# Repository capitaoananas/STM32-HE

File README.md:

# STM 32 HE

A silly [hall effect](https://en.wikipedia.org/wiki/Hall_effect) split keyboard with a built in [STM32F446RET6](https://lcsc.com/product-detail/Microcontrollers-MCU-MPU-SOC_ST-STM32F446RET6_C69336.html?s_z=n_STM32F446RET6) that runs on the [libhmk](https://github.com/peppapighs/libhmk) firmware!

Schematic             |  PCB
:-------------------------:|:-------------------------:
  |  

If you really want to crunch in on those errors check the [kicanvas](https://kicanvas.org/?github=https%3A%2F%2Fgithub.com%2Fcapitaoananas%2FSTM32-HE%2Fblob%2Fmain%2Fkicad%2Fstm32-he.kicad_pro) file

---

## Hardware:

- STM32F446RET6
- OH49E-S
- SN74LV4051A
- TC2030
- TYPE-C-31-M-12
- USBLC6-2SC6
- X322516MLB4SI

---

This project is still a WIP

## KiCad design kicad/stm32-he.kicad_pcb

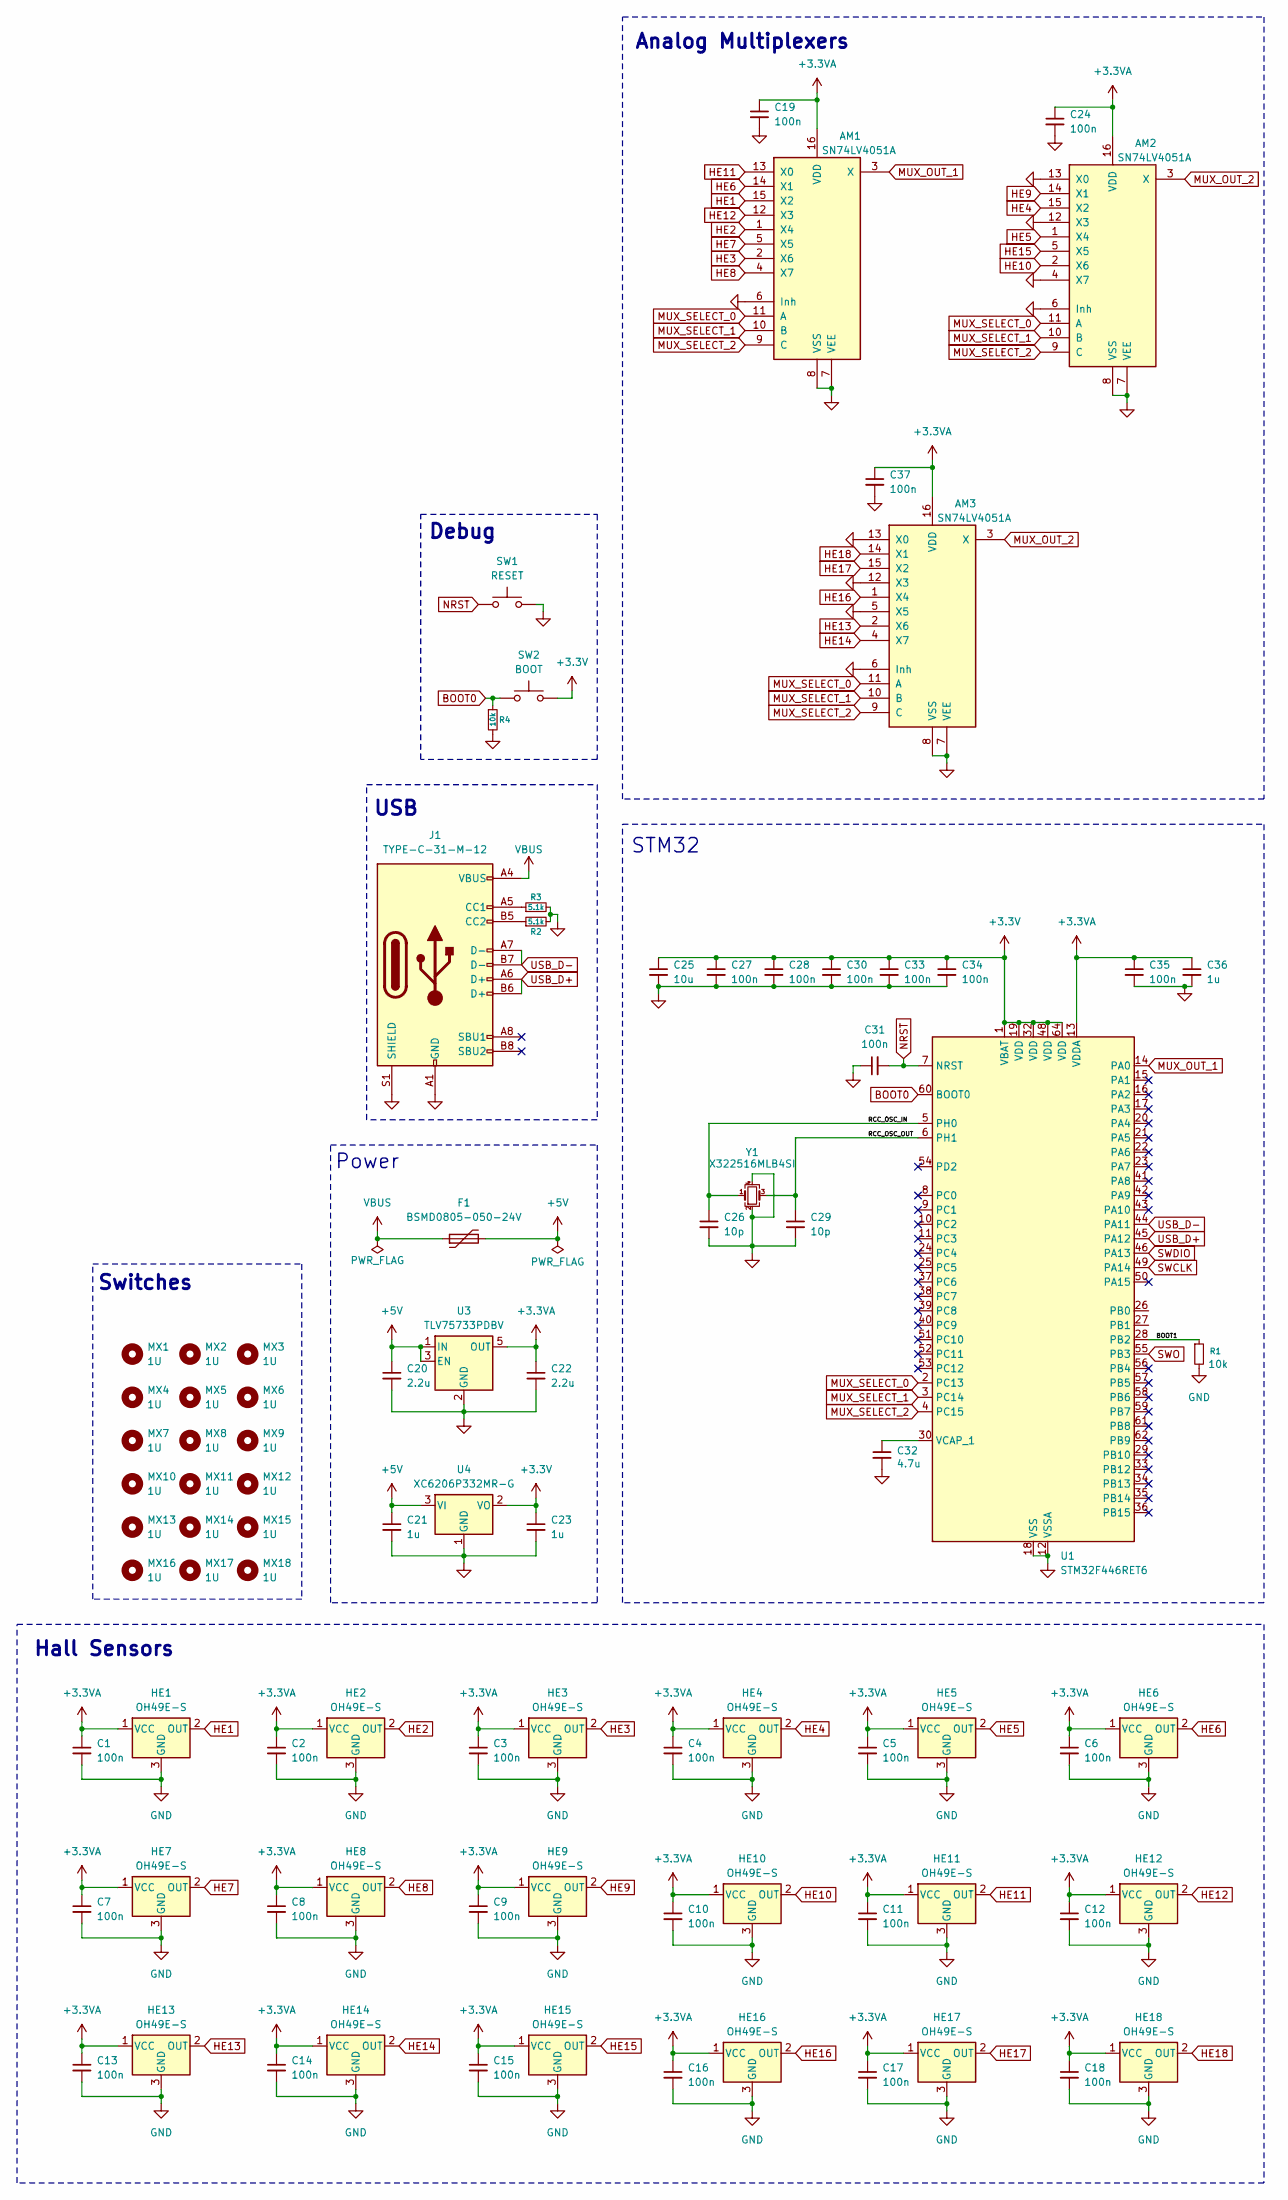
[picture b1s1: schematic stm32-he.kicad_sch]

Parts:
AM1, AM2, AM3: SN74LV4051A; TSSOP-16_4.4x5mm_P0.65mm
C1, C2, C3, C4, C5, C6, C7, C8, C9, C10, C11, C12, C13, C14, C15, C16, C17, C18, C19, C24, C27, C28, C30, C31, C33, C34, C35, C37: 100n; C_0402_1005Metric
C20, C22: 2.2u; C_0603_1608Metric
C21, C23, C36: 1u; C_0603_1608Metric
C25: 10u; C_0603_1608Metric
C26, C29: 10p; C_0402_1005Metric
C32: 4.7u; C_0603_1608Metric
F1: BSMD0805-050-24V; Fuse_0805_2012Metric
HE1, HE2, HE3, HE4, HE5, HE6, HE7, HE8, HE9, HE10, HE11, HE12, HE13, HE14, HE15, HE16, HE17, HE18: OH49E-S; SOT-23-3
J1: TYPE-C-31-M-12; USB_C_Receptacle_HRO_TYPE-C-31-M-12
MX1, MX2, MX3, MX4, MX5, MX6, MX7, MX8, MX9, MX10, MX11, MX12, MX13, MX14, MX15, MX16, MX17, MX18: 1U; MX-1U
R1, R4: 10k; R_0402_1005Metric
R2, R3: 5.1k; R_0402_1005Metric
SW1: RESET; SW_Push_1P1T_NO_CK_KMR2
SW2: BOOT; SW_Push_1P1T_NO_CK_KMR2
U1: STM32F446RET6; LQFP-64_10x10mm_P0.5mm
U3: TLV75733PDBV; SOT-23-5
U4: XC6206P332MR-G; SOT-23-3
Y1: X322516MLB4SI; Crystal_SMD_3225-4Pin_3.2x2.5mm

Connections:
+3.3V: C23.1, C25.1, C27.1, C28.1, C30.1, C33.1, C34.1, SW2.2, U1.1 (VBAT), U1.19 (VDD), U1.32 (VDD), U1.48 (VDD), U1.64 (VDD), U4.2 (VO)
+3.3VA: AM1.16 (VDD), AM2.16 (VDD), AM3.16 (VDD), C1.1, C2.1, C3.1, C4.1, C5.1, C6.1, C7.1, C8.1, C9.1, C10.1, C11.1, C12.1, C13.1, C14.1, C15.1, C16.1, C17.1, C18.1, C19.1, C22.1, C24.1, C35.1, C36.1, C37.1, HE1.1 (VCC), HE2.1 (VCC), HE3.1 (VCC), HE4.1 (VCC), HE5.1 (VCC), HE6.1 (VCC), HE7.1 (VCC), HE8.1 (VCC), HE9.1 (VCC), HE10.1 (VCC), HE11.1 (VCC), HE12.1 (VCC), HE13.1 (VCC), HE14.1 (VCC), HE15.1 (VCC), HE16.1 (VCC), HE17.1 (VCC), HE18.1 (VCC), U1.13 (VDDA), U3.5 (OUT)
+5V: C20.1, C21.1, F1.2, U3.1 (IN), U3.3 (EN), U4.3 (VI)
/BOOT1: R1.1, U1.28 (PB2)
/RCC_OSC_IN: C26.1, U1.5 (PH0), Y1.1
/RCC_OSC_OUT: C29.1, U1.6 (PH1), Y1.3
BOOT0: R4.1, SW2.1, U1.60 (BOOT0)
GND: AM1.6 (Inh), AM1.7 (VEE), AM1.8 (VSS), AM2.4 (X7), AM2.6 (Inh), AM2.7 (VEE), AM2.8 (VSS), AM2.12 (X3), AM2.13 (X0), AM3.5 (X5), AM3.6 (Inh), AM3.7 (VEE), AM3.8 (VSS), AM3.12 (X3), AM3.13 (X0), C1.2, C2.2, C3.2, C4.2, C5.2, C6.2, C7.2, C8.2, C9.2, C10.2, C11.2, C12.2, C13.2, C14.2, C15.2, C16.2, C17.2, C18.2, C19.2, C20.2, C21.2, C22.2, C23.2, C24.2, C25.2, C26.2, C27.2, C28.2, C29.2, C30.2, C31.1, C32.2, C33.2, C34.2, C35.2, C36.2, C37.2, HE1.3 (GND), HE2.3 (GND), HE3.3 (GND), HE4.3 (GND), HE5.3 (GND), HE6.3 (GND), HE7.3 (GND), HE8.3 (GND), HE9.3 (GND), HE10.3 (GND), HE11.3 (GND), HE12.3 (GND), HE13.3 (GND), HE14.3 (GND), HE15.3 (GND), HE16.3 (GND), HE17.3 (GND), HE18.3 (GND), J1.A1 (GND), J1.A12 (GND), J1.B1 (GND), J1.B12 (GND), J1.S1 (SHIELD), R1.2, R2.2, R3.2, R4.2, SW1.2, U1.12 (VSSA), U1.18 (VSS), U1.31 (VSS), U1.47 (VSS), U1.63 (VSS), U3.2 (GND), U4.1 (GND), Y1.2, Y1.4
HE1: AM1.15 (X2), HE1.2 (OUT)
HE2: AM1.1 (X4), HE2.2 (OUT)
HE3: AM1.2 (X6), HE3.2 (OUT)
HE4: AM2.15 (X2), HE4.2 (OUT)
HE5: AM2.1 (X4), HE5.2 (OUT)
HE6: AM1.14 (X1), HE6.2 (OUT)
HE7: AM1.5 (X5), HE7.2 (OUT)
HE8: AM1.4 (X7), HE8.2 (OUT)
HE9: AM2.14 (X1), HE9.2 (OUT)
HE10: AM2.2 (X6), HE10.2 (OUT)
HE11: AM1.13 (X0), HE11.2 (OUT)
HE12: AM1.12 (X3), HE12.2 (OUT)
HE13: AM3.2 (X6), HE13.2 (OUT)
HE14: AM3.4 (X7), HE14.2 (OUT)
HE15: AM2.5 (X5), HE15.2 (OUT)
HE16: AM3.1 (X4), HE16.2 (OUT)
HE17: AM3.15 (X2), HE17.2 (OUT)
HE18: AM3.14 (X1), HE18.2 (OUT)
MUX_OUT_1: AM1.3 (X), U1.14 (PA0)
MUX_OUT_2: AM2.3 (X), AM3.3 (X)
MUX_SELECT_0: AM1.11 (A), AM2.11 (A), AM3.11 (A), U1.2 (PC13)
MUX_SELECT_1: AM1.10 (B), AM2.10 (B), AM3.10 (B), U1.3 (PC14)
MUX_SELECT_2: AM1.9 (C), AM2.9 (C), AM3.9 (C), U1.4 (PC15)
NRST: C31.2, SW1.1, U1.7 (NRST)
unnamed: J1.A5 (CC1), R3.1
unnamed: J1.B5 (CC2), R2.1
unnamed: C32.1, U1.30 (VCAP_1)
SWCLK: U1.49 (PA14)
SWDIO: U1.46 (PA13)
SWO: U1.55 (PB3)
USB_D+: J1.A6 (D+), J1.B6 (D+), U1.45 (PA12)
USB_D-: J1.A7 (D-), J1.B7 (D-), U1.44 (PA11)
VBUS: F1.1, J1.A4 (VBUS), J1.A9 (VBUS), J1.B4 (VBUS), J1.B9 (VBUS)

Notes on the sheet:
Analog Multiplexers
STM32
USB
Power
Switches
Hall Sensors
Debug

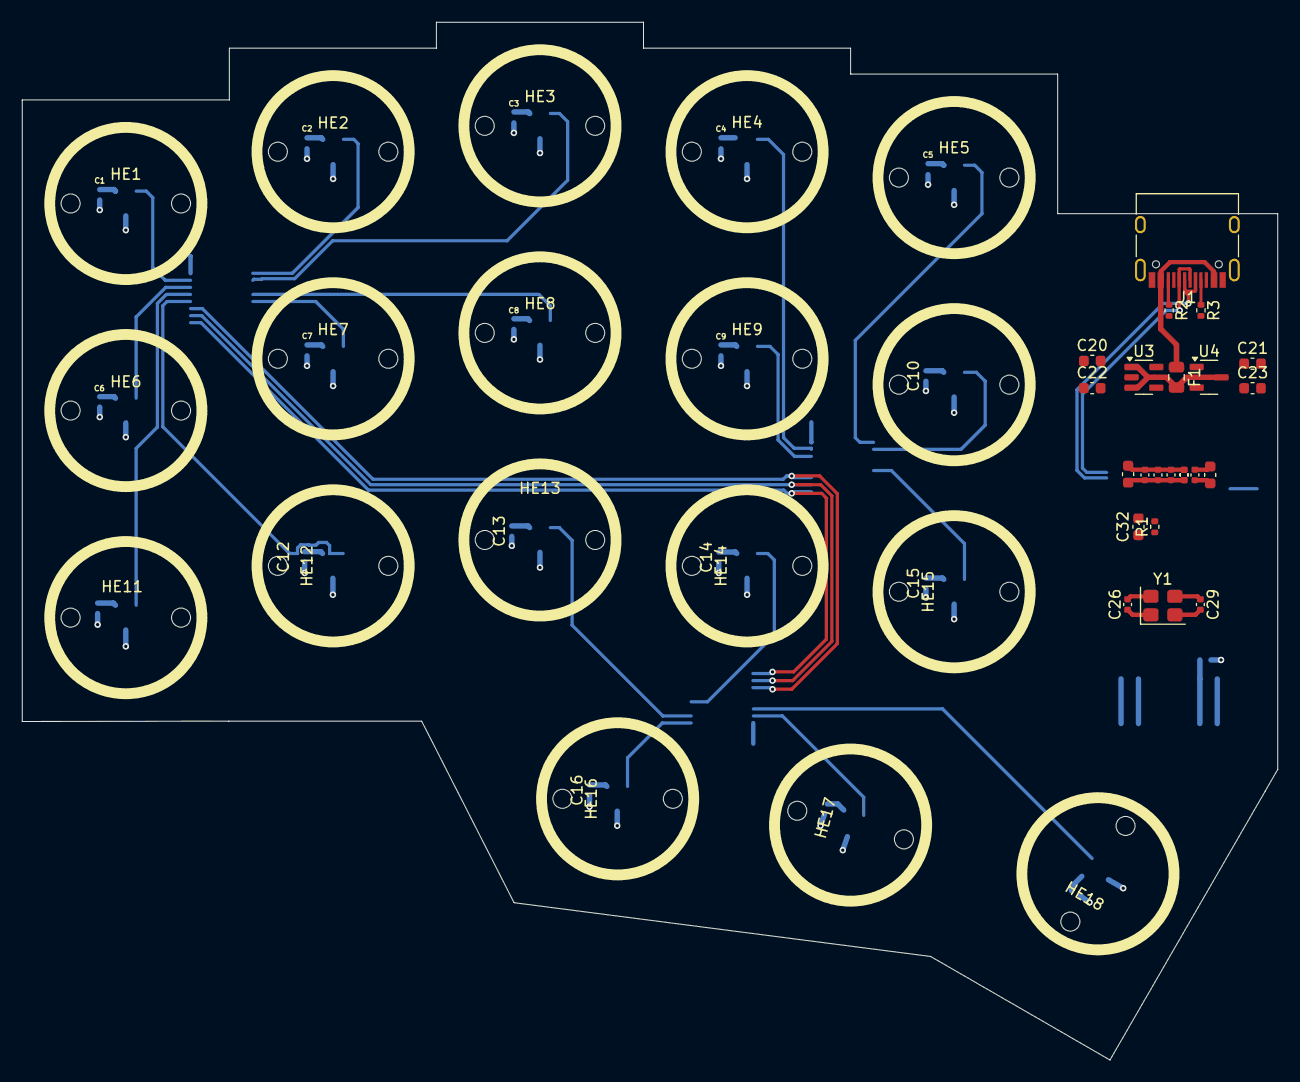
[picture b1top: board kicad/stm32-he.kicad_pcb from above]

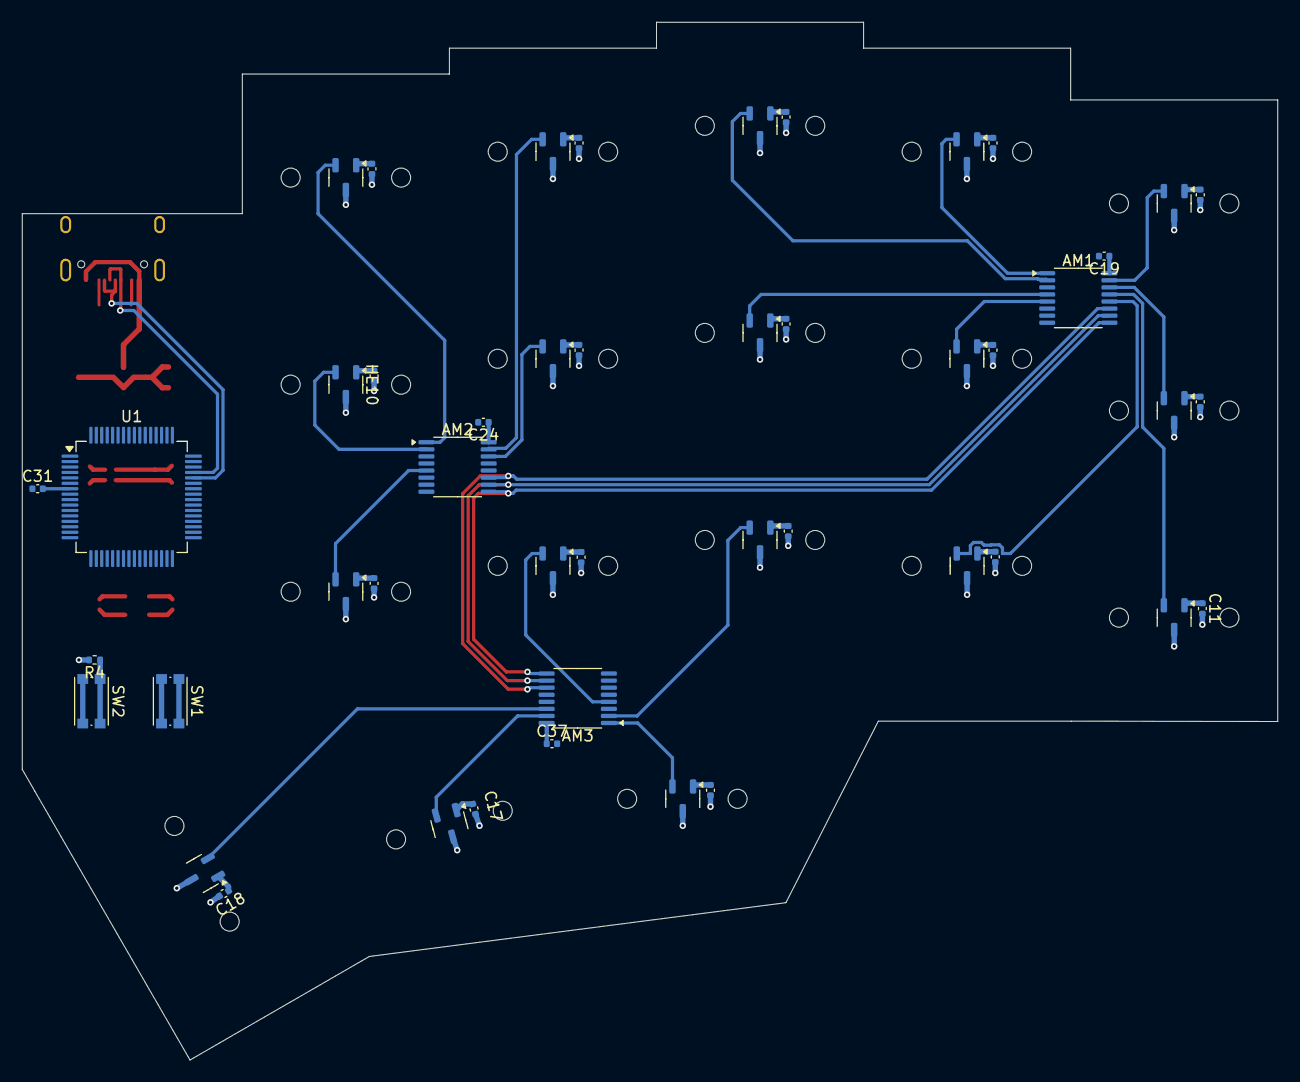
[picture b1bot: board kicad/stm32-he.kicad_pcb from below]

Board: 2 copper layers, 115.5 x 95.5 mm, 88 parts (47 on the bottom side), 38 nets.

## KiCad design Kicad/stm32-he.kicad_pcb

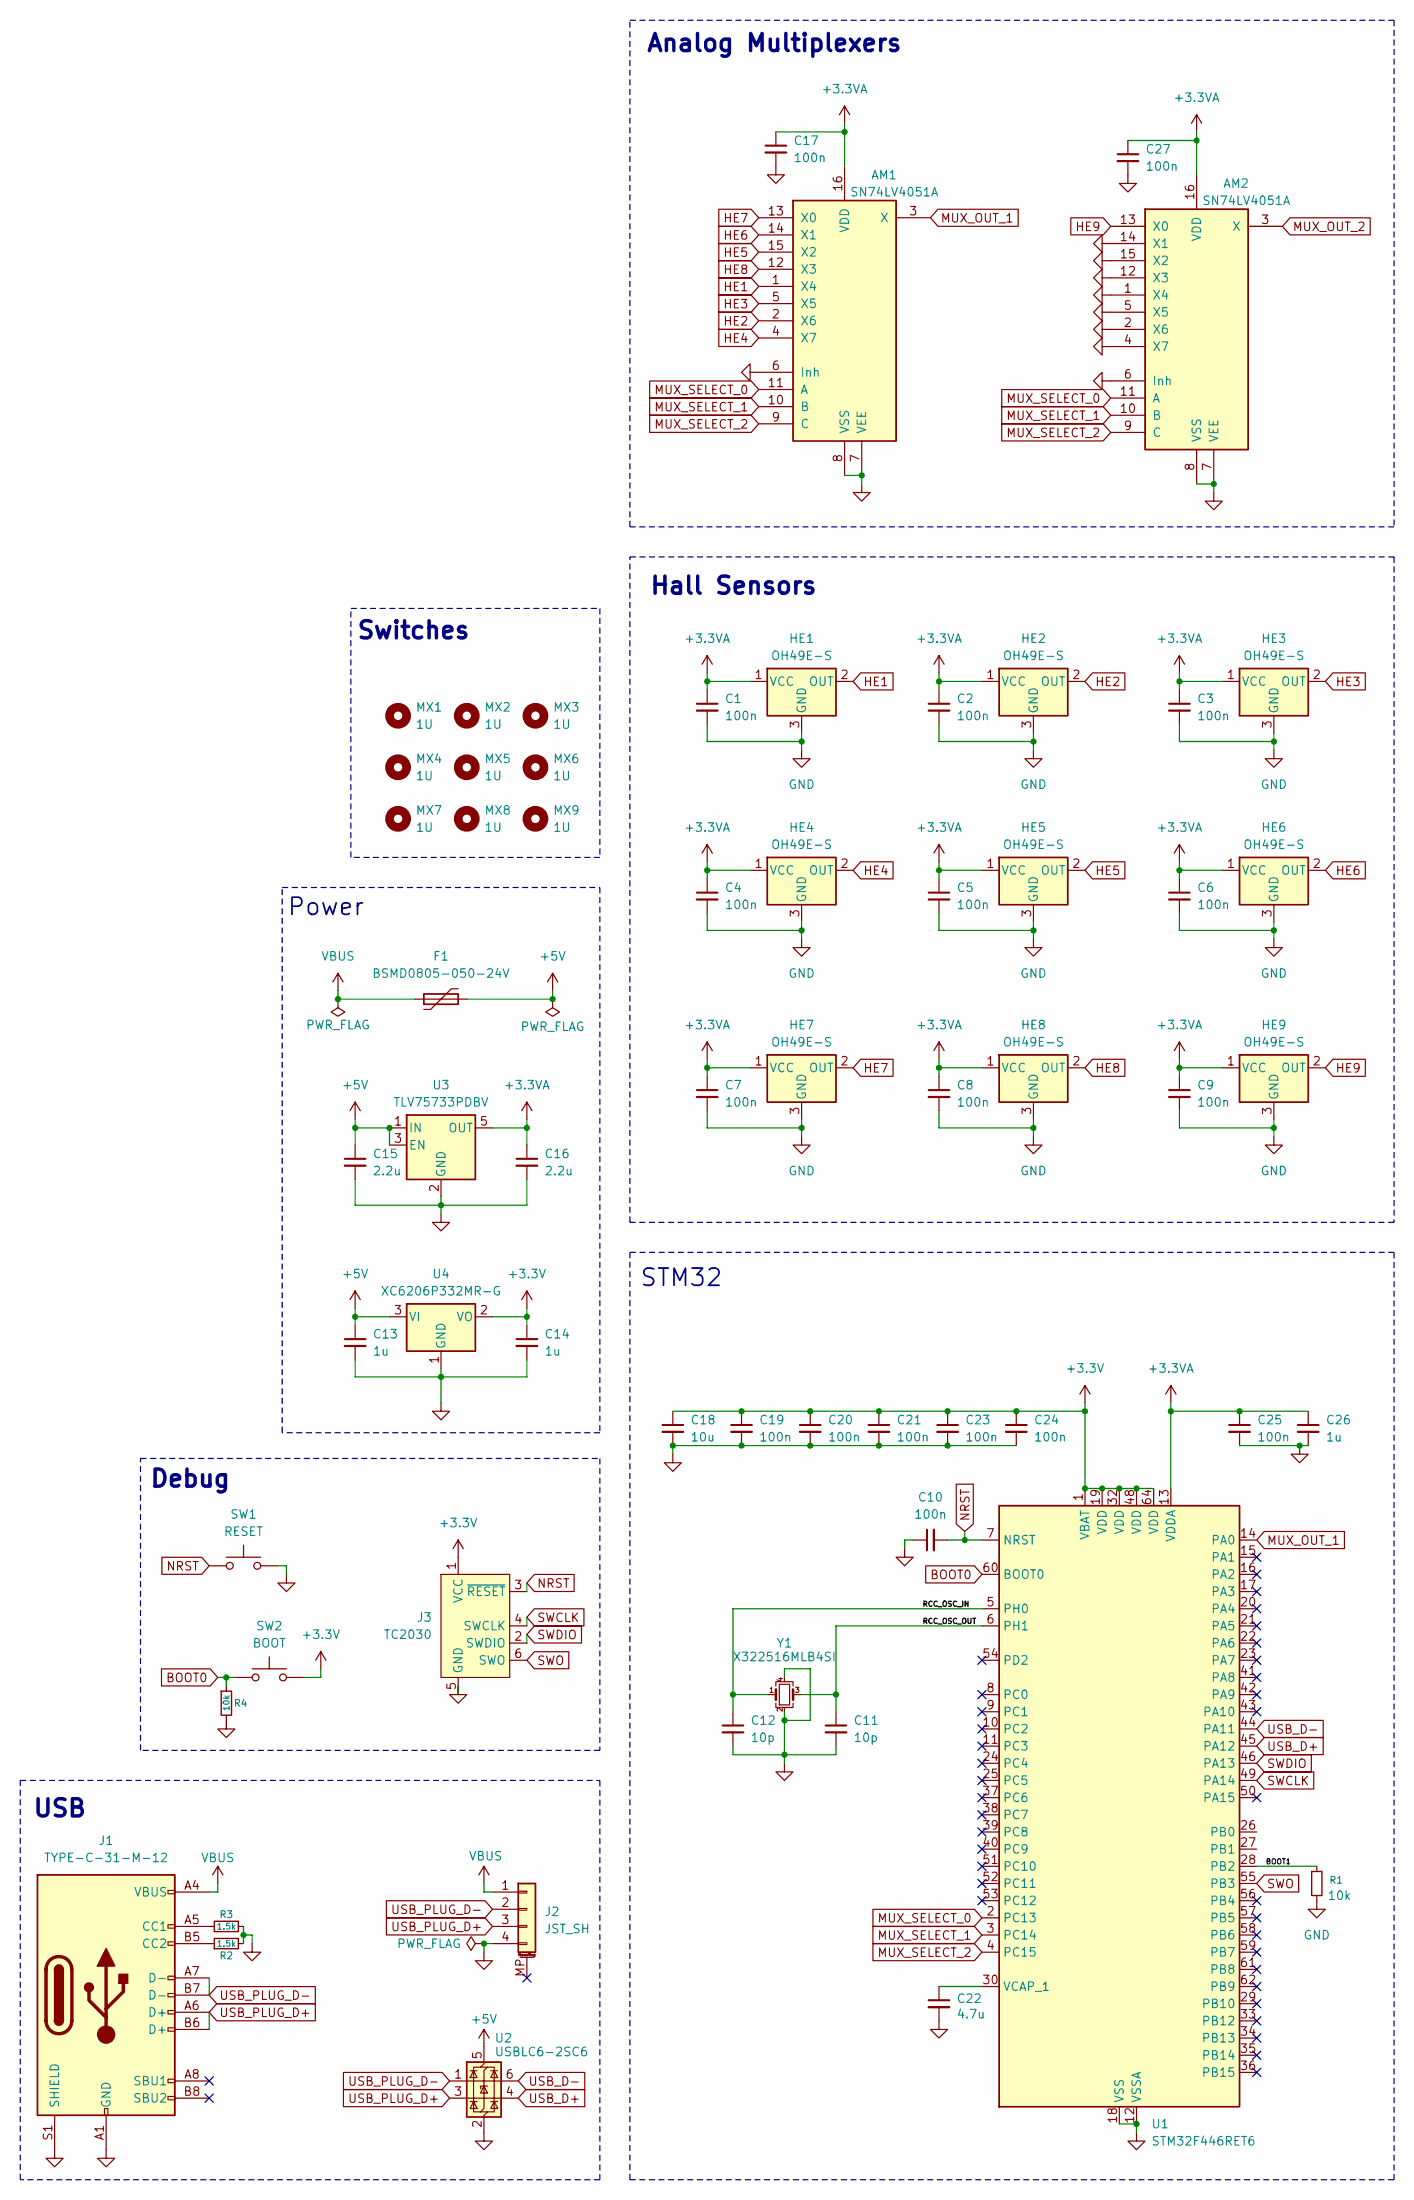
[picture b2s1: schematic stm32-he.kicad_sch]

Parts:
AM1, AM2: SN74LV4051A; TSSOP-16_4.4x5mm_P0.65mm
C1, C2, C3, C4, C5, C6, C7, C8, C9, C10, C17, C19, C20, C21, C23, C24, C25, C27: 100n; C_0402_1005Metric
C11, C12: 10p; C_0402_1005Metric
C13, C14, C26: 1u; C_0603_1608Metric
C15, C16: 2.2u; C_0603_1608Metric
C18: 10u; C_0603_1608Metric
C22: 4.7u; C_0603_1608Metric
F1: BSMD0805-050-24V; Fuse_0805_2012Metric
HE1, HE2, HE3, HE4, HE5, HE6, HE7, HE8, HE9: OH49E-S; SOT-23-3
J1: TYPE-C-31-M-12; USB_C_Receptacle_HRO_TYPE-C-31-M-12
J2: JST_SH; JST_SH_SM04B-SRSS-TB_1x04-1MP_P1.00mm_Horizontal
J3: TC2030; Tag-Connect_TC2030-IDC-FP_2x03_P1.27mm_Vertical
MX1, MX2, MX3, MX4, MX5, MX6, MX7, MX8, MX9: 1U; MX-1U
R1, R4: 10k; R_0402_1005Metric
R2, R3: 1.5k; R_0402_1005Metric
SW1: RESET; SW_Push_1P1T_NO_CK_KMR2
SW2: BOOT; SW_Push_1P1T_NO_CK_KMR2
U1: STM32F446RET6; LQFP-64_10x10mm_P0.5mm
U2: USBLC6-2SC6; SOT-23-6
U3: TLV75733PDBV; SOT-23-5
U4: XC6206P332MR-G; SOT-23-3
Y1: X322516MLB4SI; Crystal_SMD_3225-4Pin_3.2x2.5mm

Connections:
+3.3V: C14.1, C18.1, C19.1, C20.1, C21.1, C23.1, C24.1, J3.1 (VCC), SW2.2, U1.1 (VBAT), U1.19 (VDD), U1.32 (VDD), U1.48 (VDD), U1.64 (VDD), U4.2 (VO)
+3.3VA: AM1.16 (VDD), AM2.16 (VDD), C1.1, C2.1, C3.1, C4.1, C5.1, C6.1, C7.1, C8.1, C9.1, C16.1, C17.1, C25.1, C26.1, C27.1, HE1.1 (VCC), HE2.1 (VCC), HE3.1 (VCC), HE4.1 (VCC), HE5.1 (VCC), HE6.1 (VCC), HE7.1 (VCC), HE8.1 (VCC), HE9.1 (VCC), U1.13 (VDDA), U3.5 (OUT)
+5V: C13.1, C15.1, F1.2, U2.5 (VBUS), U3.1 (IN), U3.3 (EN), U4.3 (VI)
/BOOT1: R1.1, U1.28 (PB2)
/RCC_OSC_IN: C12.1, U1.5 (PH0), Y1.1
/RCC_OSC_OUT: C11.1, U1.6 (PH1), Y1.3
BOOT0: R4.1, SW2.1, U1.60 (BOOT0)
GND: AM1.6 (Inh), AM1.7 (VEE), AM1.8 (VSS), AM2.1 (X4), AM2.2 (X6), AM2.4 (X7), AM2.5 (X5), AM2.6 (Inh), AM2.7 (VEE), AM2.8 (VSS), AM2.12 (X3), AM2.14 (X1), AM2.15 (X2), C1.2, C2.2, C3.2, C4.2, C5.2, C6.2, C7.2, C8.2, C9.2, C10.1, C11.2, C12.2, C13.2, C14.2, C15.2, C16.2, C17.2, C18.2, C19.2, C20.2, C21.2, C22.2, C23.2, C24.2, C25.2, C26.2, C27.2, HE1.3 (GND), HE2.3 (GND), HE3.3 (GND), HE4.3 (GND), HE5.3 (GND), HE6.3 (GND), HE7.3 (GND), HE8.3 (GND), HE9.3 (GND), J1.A1 (GND), J1.A12 (GND), J1.B1 (GND), J1.B12 (GND), J1.S1 (SHIELD), J2.4, J3.5 (GND), R1.2, R2.2, R3.2, R4.2, SW1.2, U1.12 (VSSA), U1.18 (VSS), U1.31 (VSS), U1.47 (VSS), U1.63 (VSS), U2.2 (GND), U3.2 (GND), U4.1 (GND), Y1.2, Y1.4
HE1: AM1.1 (X4), HE1.2 (OUT)
HE2: AM1.2 (X6), HE2.2 (OUT)
HE3: AM1.5 (X5), HE3.2 (OUT)
HE4: AM1.4 (X7), HE4.2 (OUT)
HE5: AM1.15 (X2), HE5.2 (OUT)
HE6: AM1.14 (X1), HE6.2 (OUT)
HE7: AM1.13 (X0), HE7.2 (OUT)
HE8: AM1.12 (X3), HE8.2 (OUT)
HE9: AM2.13 (X0), HE9.2 (OUT)
MUX_OUT_1: AM1.3 (X), U1.14 (PA0)
MUX_OUT_2: AM2.3 (X)
MUX_SELECT_0: AM1.11 (A), AM2.11 (A), U1.2 (PC13)
MUX_SELECT_1: AM1.10 (B), AM2.10 (B), U1.3 (PC14)
MUX_SELECT_2: AM1.9 (C), AM2.9 (C), U1.4 (PC15)
NRST: C10.2, J3.3 (~RESET), SW1.1, U1.7 (NRST)
unnamed: J1.A5 (CC1), R3.1
unnamed: J1.B5 (CC2), R2.1
unnamed: C22.1, U1.30 (VCAP_1)
SWCLK: J3.4 (SWCLK), U1.49 (PA14)
SWDIO: J3.2 (SWDIO), U1.46 (PA13)
SWO: J3.6 (SWO), U1.55 (PB3)
USB_D+: U1.45 (PA12), U2.4 (I/O2)
USB_D-: U1.44 (PA11), U2.6 (I/O1)
USB_PLUG_D+: J1.A6 (D+), J1.B6 (D+), J2.3, U2.3 (I/O2)
USB_PLUG_D-: J1.A7 (D-), J1.B7 (D-), J2.2, U2.1 (I/O1)
VBUS: F1.1, J1.A4 (VBUS), J1.A9 (VBUS), J1.B4 (VBUS), J1.B9 (VBUS), J2.1

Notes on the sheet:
Analog Multiplexers
STM32
USB
Power
Switches
Hall Sensors
Debug

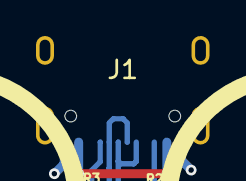
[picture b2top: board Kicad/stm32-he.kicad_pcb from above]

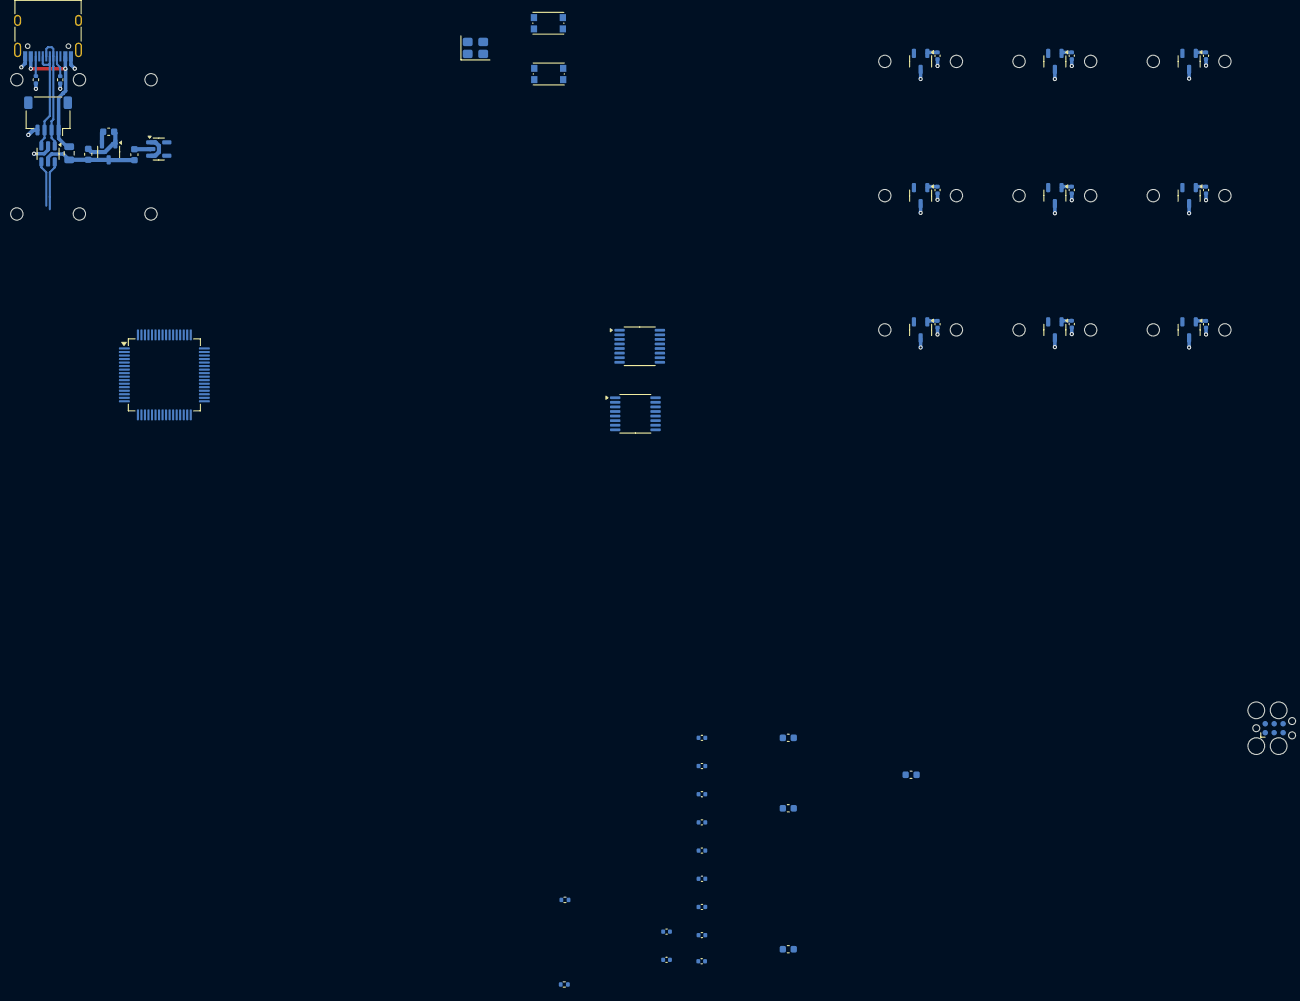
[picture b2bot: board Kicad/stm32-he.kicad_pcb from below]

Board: 2 copper layers, 66 parts (53 on the bottom side), 33 nets.

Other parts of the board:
MX1#2, MX1#3, MX2#2, MX2#3: 1U; MX-1U
